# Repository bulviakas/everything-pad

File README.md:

# Everything pad - Custom macropad
A macropad project for the __Blueprint program__ by [Hack Club](https://hackclub.com/). 

The mini-keyboard features: 
  * 6 programmable keys
  * Rotary encoder
  * 8 RGB LEDs for backlight
  * OLED display

Designed to be a helpful tool while editing, gaming or just deep in flow state. ***The main goal - versatility***: multiple modes for every needed occasion (system sound control, application shortcuts, backlight configuration).

### Tools

* **PCB**: Custom-designed using **KiCad**
* **Case**: Modeled in **SolidWorks**
* **Firmware**: Built with **QMK**, supporting multiple layers, RGB lighting, encoder input, and OLED display

### Status
(2026-03-31) Project still in progress - no physical testing yet!

## PCB
### Schematic view

The keys and the rotary encoder are connected in a matrix.

### The product itself

A personal character Steve was made with **Inkscape**. Everyting is connected over 2 layers, with 0.4mm traces and GND fields. SK6812-MINI-E LED footprints were modified due to clearance errors.

## CAD model

The assembly process is quite simple - the PCB is mounted onto the bottom part of the case with 2 M3 bolts and heatset inserts. Top cover just slides in from the top.

## Firmware

As of now, the code is purely theoretical, since there is no way to test it. However, _in theory_, the keyboard has 3 modes:
* **System sound control** - play/pause music, increase/decrease volume, mute, etc.
* **Application shortcuts** - case-specific keybinds, eg. Discord toggle mute, toggle camera
* **RBG backlight configuration** - increase/decrease brightness, hue, etc.

The colour of the RBG backlight shows the currently active mode (SSC - Blue, Apps - Green, etc.). OLED display serves as the main info output when switching modes. Since the macropad cannot read real system sound values, it stores simulated volume and displays a simple bar on-screen when relevant.

## BOM
 A list of everything used to make this masterpiece:
 * 1x Seeed XIAO RP2040
 * 7x through-hole 1N4148 Diodes
 * 6x MX-Style switches
 * 1x EC11 Rotary encoder
 * 1x 0.91 inch OLED display (GND-VCC-SCL-SDA)
 * 6x white blank DSA keycaps
 * 8x SK6812 MINI-E LEDs
 * 2x M3x16mm screws
 * 2x M3x5mx4mm heatset inserts
 * 1x case (2 printed parts)
 * 1x printed knob for the encoder
 * Some joy and whimsy~

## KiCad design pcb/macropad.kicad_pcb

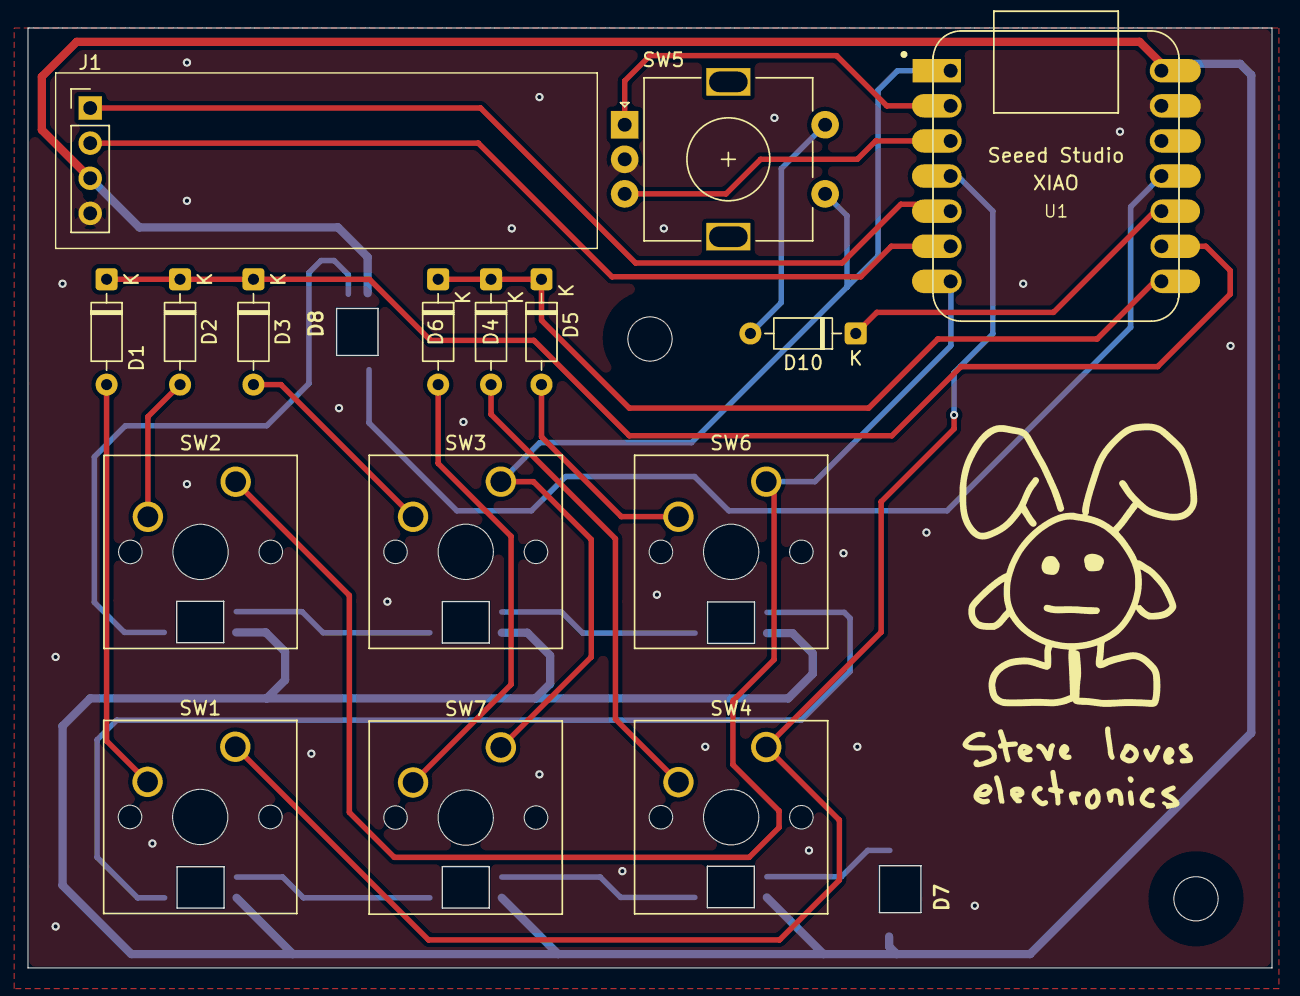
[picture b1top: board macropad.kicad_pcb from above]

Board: 2 copper layers, 90.0 x 68.0 mm, 24 parts (0 on the bottom side), 27 nets.

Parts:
D1, D2, D3, D4, D5, D6, D10: D; D_DO-35_SOD27_P7.62mm_Horizontal
D7, D8: WS2812B; SK6812MINI-E_fixed
D9: WS2812B; MX_SK6812MINI-E
D11, D12, D13, D14, D15: SK6812MINI-E; MX_SK6812MINI-E
J1: OLED_DISPLAY; PinHeader_1x04_P2.54mm_Vertical
SW1, SW2, SW3, SW4, SW6, SW7: SW_Push; SW_Cherry_MX_1.00u_PCB
SW5: RotaryEncoder_Switch; RotaryEncoder_Alps_EC11E-Switch_Vertical_H20mm
U1: Seeed Studio XIAO RP2040; XIAO-Generic-Hybrid-14P-2.54-21X17.8MM

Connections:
Column 1: SW1.1, SW4.1, U1.4 (PA11_A3_D3)
Column 2: SW2.1, SW6.1, U1.7 (PB08_A6_D6_TX)
Column 3: SW3.1, SW5.S1, SW7.1, U1.1 (PA02_A0_D0)
EN_A: SW5.A, U1.2 (PA4_A1_D1)
EN_B: SW5.B, U1.3 (PA10_A2_D2)
GND: D7.1 (VSS), D8.1 (VSS), D9.1 (VSS), D11.1 (VSS), D12.1 (VSS), D13.1 (VSS), D14.1 (VSS), D15.1 (VSS), J1.4, SW5.C, U1.13 (GND)
LED-IN: D8.2 (DIN), U1.11 (PA6_A10_D10_MOSI)
unnamed: D1.2 (A), SW1.2
unnamed: D2.2 (A), SW2.2
unnamed: D3.2 (A), SW3.2
unnamed: D4.2 (A), SW4.2
unnamed: D5.2 (A), SW6.2
unnamed: D6.2 (A), SW7.2
unnamed: D8.4 (DOUT), D9.2 (DIN)
unnamed: D10.2 (A), SW5.S2
unnamed: D9.4 (DOUT), D11.2 (DIN)
unnamed: D11.4 (DOUT), D12.2 (DIN)
unnamed: D12.4 (DOUT), D13.2 (DIN)
unnamed: D13.4 (DOUT), D14.2 (DIN)
unnamed: D14.4 (DOUT), D15.2 (DIN)
unnamed: D7.2 (DIN), D15.4 (DOUT)
Row 1: D1.1 (K), D2.1 (K), D3.1 (K), U1.9 (PA7_A8_D8_SCK)
Row 2: D4.1 (K), D5.1 (K), D6.1 (K), U1.8 (PB09_A7_D7_RX)
Row 3: D10.1 (K), U1.10 (PA5_A9_D9_MISO)
SCL: J1.2, U1.6 (PA9_A5_D5_SCL)
SDA: J1.1, U1.5 (PA8_A4_D4_SDA)
VCC: D7.3 (VDD), D8.3 (VDD), D9.3 (VDD), D11.3 (VDD), D12.3 (VDD), D13.3 (VDD), D14.3 (VDD), D15.3 (VDD), J1.3, U1.14 (5V)

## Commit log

2026-03-25 Created the PCB with all needed basic functionalities
2026-03-26 V1.2 - Fixed the LED symbols and retraced everything
2026-03-27 V1.3 - Added switch LEDs and GND fields
2026-03-27 .gitignore update
2026-03-27 Imported graphics for the PCB
2026-03-27 Updated libraries
2026-03-27 V1.4 - Reworked GND fields, solved all errors, added Steve
2026-03-31 Moved the KiCad libraries. Added the CAD case elements
2026-03-31 Added case production STEP files
2026-03-31 Created new keyboard config
2026-03-31 V1.5 - Fixed faulty encoder wiring, retraced
2026-03-31 Added firmware production files
2026-03-31 New firmware files. Custom keyboard and keymap 'multimode'
2026-03-31 Created assets for the README
2026-03-31 Updated the README.md file
2026-03-31 Cleaned up the folder structure a bit
2026-03-31 Updated README.md BOM
2026-03-31 Added PCB Gerber files
